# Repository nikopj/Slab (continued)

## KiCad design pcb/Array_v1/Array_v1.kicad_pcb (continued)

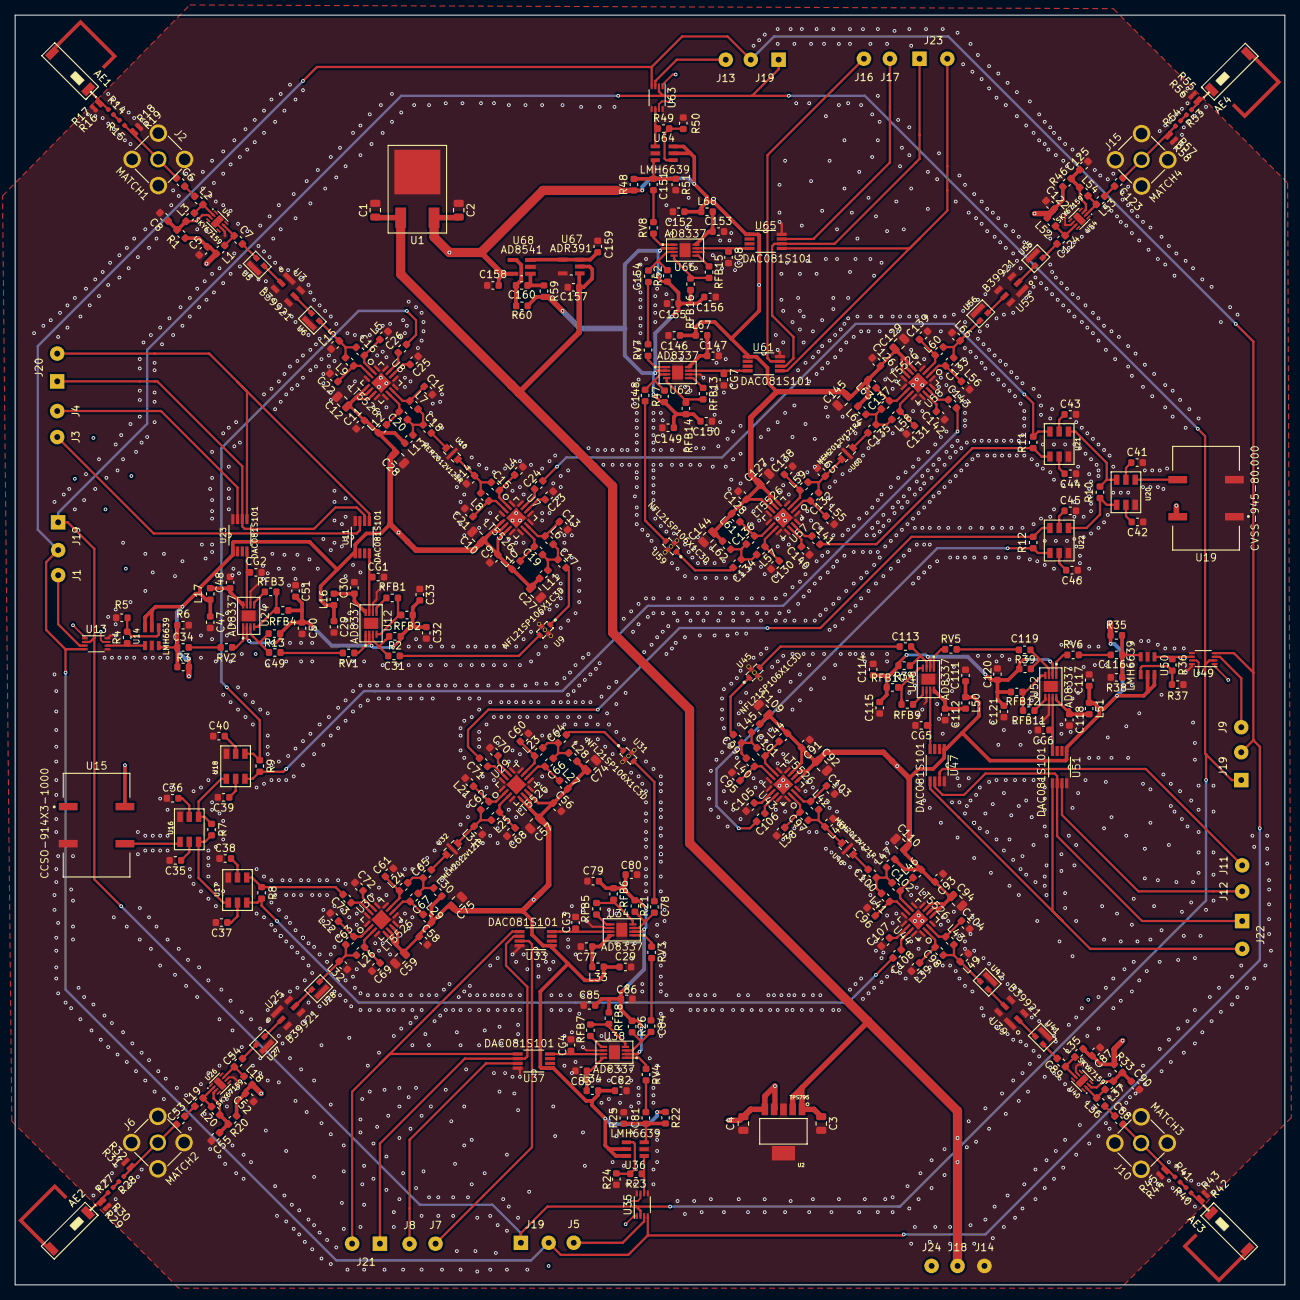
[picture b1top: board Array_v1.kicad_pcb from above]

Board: 4 copper layers, 173.9 x 173.9 mm, 419 parts (0 on the bottom side), 241 nets.

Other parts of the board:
C29#2: 10u; C_0603_1608Metric
J19#2, J19#3, J19#4: SPI_ADC; SolderWirePad_1x02_P3.81mm_Drill0.8mm

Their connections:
+5V: C29#2.1; also elsewhere on the board
GND: C29#2.2; also elsewhere on the board
SCLK_ADC: J19#2.1, J19#3.1, J19#4.1; also elsewhere on the board
~CS~_ADC: J19#2.2, J19#3.2, J19#4.2; also elsewhere on the board

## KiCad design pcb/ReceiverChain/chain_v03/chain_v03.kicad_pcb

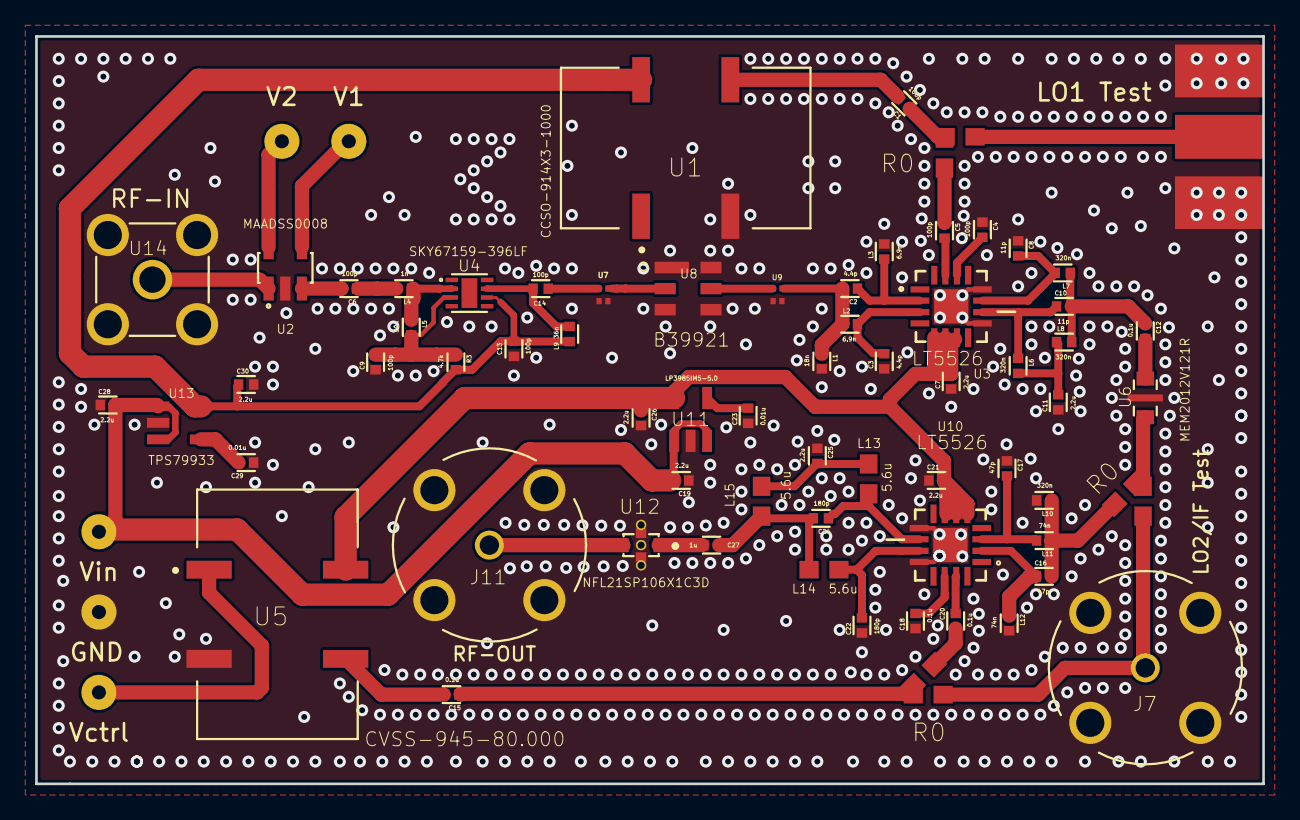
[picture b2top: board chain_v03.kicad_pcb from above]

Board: 2 copper layers, 69.8 x 42.5 mm, 74 parts (0 on the bottom side), 48 nets.

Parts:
C1, C4, C5, C6, C9, C13, C14: 100p; CAPC1005X55N
C2, C3: 4.4p; CAPC1005X55N
C7, C11, C19, C21, C25, C26, C28, C30: 2.2u; CAPC1005X55N
C8, C10: 11p; CAPC1005X55N
C12, C15, C18, C20: 0.1u; CAPC1005X55N
C16, C17: 47p; CAPC1005X55N
C22, C24: 180p; CAPC1005X55N
C23, C29: 0.01u; CAPC1005X55N
C27: 1u; CAPC1005X55N
GND: Conn_01x01_Female; SolderWirePad_1x01_Drill0.8mm
J7: LO2/IF Test; TE_5-1634503-1
J11: RF-OUT; TE_5-1634503-1
L1: 18n; CAPC1005X55N
L2, L3: 6.9n; CAPC1005X55N
L4: 1n; CAPC1005X55N
L5: 30n; CAPC1005X55N
L6, L7, L8, L10: 320n; CAPC1005X55N
L9: 36n; CAPC1005X55N
L11, L12: 74n; CAPC1005X55N
L13, L14, L15: 5.6u; 0603
LO1 Test: LO1 Test; sma-edge-16
R0, R0#2, R0#3, R1, R5, R7: 0; 0603
R3: 4.7k; CAPC1005X55N
U1: CCSO-914X3-1000; OSCSC508P1420X914X530-4N
U2: MAADSS0008; SOT95P285X145-5N
U3, U10: LT5526; QFN65P400X400X100-17N
U4: SKY67159-396LF; SON50P200X200X80-9N
U5: CVSS-945-80.000; OSCSC508P1420X914X530-4N
U6: MEM2012V121R; FIL_MEM2012V121RT001
U7, U9: PAT0510S
U8: B39921; SON120P300X300X110-6N
U11: LP3985IM5-5.0; SOT95P300X120-5N
U12: NFL21SP106X1C3D; FIL_NFM21PC105B1C3D
U13: TPS79933; SOT95P300X120-5N
U14: RF-IN; TE_5-1814832-1
V1, V2: Conn_01x01_Female; SolderWirePad_1x01_Drill0.8mm
Vctrl: Conn_01x01_Female; SolderWirePad_1x01_Drill0.8mm
Vin: Conn_01x01_Female; SolderWirePad_1x01_Drill0.8mm

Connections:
+3V3: C13.2, C30.1, L9.1, R3.2, U1.4, U4.6, U13.5
+5V: C7.2, C21.2, C26.1, U3.5, U3.6, U3.7, U5.4, U10.5, U10.6, U10.7, U11.5
GND: C3.1, C4.1, C7.1, C8.1, C9.1, C11.1, C13.1, C17.1, C18.1, C19.1, C21.1, C22.1, C23.1, C25.1, C26.2, C28.1, C29.1, C30.2, GND.1, J7.2, J7.3, J7.4, J7.5, J11.2, J11.3, J11.4, J11.5, L1.2, L3.2, L10.2, L12.2, LO1 Test.1, LO1 Test.3, LO1 Test.4, LO1 Test.5, U1.2, U2.2, U3.9, U3.12, U3.17, U5.2, U6.2, U7.3, U8.1, U8.3, U8.4, U8.6, U9.3, U10.9, U10.12, U10.17, U11.2, U12.2_1, U12.2_2, U12.S1, U12.S2, U12.S3, U13.2, U14.2, U14.3, U14.4, U14.5
LO2: C20.1, R0#2.1
unnamed: C1.1, R0.1, R1.2
unnamed: C1.2, U1.3
unnamed: C2.1, L3.1, U3.2
unnamed: C3.2, L2.2, U3.3
unnamed: C4.2, U3.14
unnamed: C5.1, R1.1
unnamed: C5.2, U3.15
unnamed: C6.1, L4.2
unnamed: C6.2, U2.3
unnamed: C8.2, L7.2, U3.11
unnamed: C9.2, L5.2, R3.1, U4.3
unnamed: C10.1, L6.1, U3.10
unnamed: C10.2, C12.1, L7.1, L8.2
unnamed: C11.2, L6.2, L8.1
unnamed: C12.2, U6.1
unnamed: C14.1, U7.1
unnamed: C14.2, L9.2, U4.7
unnamed: C15.1, R0#2.2, R7.1
unnamed: C15.2, U5.3
unnamed: C16.1, L12.1, U10.2
unnamed: C16.2, L10.1, L11.1, R0#3.2
unnamed: C17.2, L11.2, U10.3
unnamed: C18.2, U10.14
unnamed: C19.2, C28.2, U11.1, U11.3, U13.1, U13.3, Vin.1
unnamed: C20.2, U10.15
unnamed: C22.2, L14.2, U10.11
unnamed: C23.2, U11.4
unnamed: C24.1, L13.1, U10.10
unnamed: C24.2, C27.1, L14.1, L15.2
unnamed: C25.2, L13.2, L15.1
unnamed: C27.2, U12.1
unnamed: C29.2, U13.4
unnamed: U2.5, V2.1
unnamed: U2.4, V1.1
unnamed: U5.1, Vctrl.1
unnamed: J7.1, R5.2, R7.2
unnamed: J11.1, U12.3
unnamed: L4.1, L5.1, U4.2
unnamed: LO1 Test.2, R0.2
unnamed: R0#3.1, R5.1, U6.3
unnamed: U7.2, U8.2
unnamed: U8.5, U9.1
unnamed: U2.1, U14.1
RFout: C2.2, L1.1, L2.1, U9.2

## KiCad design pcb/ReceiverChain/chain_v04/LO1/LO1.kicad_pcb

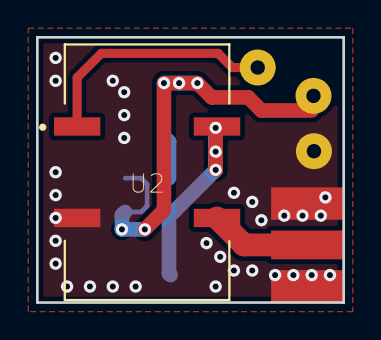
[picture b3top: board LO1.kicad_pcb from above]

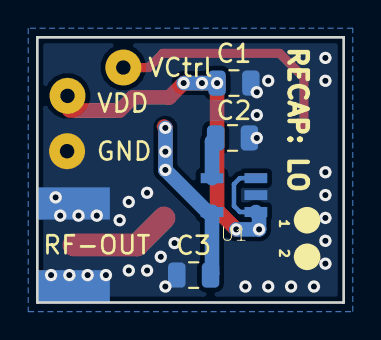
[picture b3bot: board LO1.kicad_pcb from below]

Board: 2 copper layers, 17.0 x 14.7 mm, 9 parts (4 on the bottom side), 6 nets.

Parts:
C1, C3: 2.2u; C_0805_2012Metric
C2: 0.01u; C_0805_2012Metric
GND: GND; SolderWirePad_1x01_Drill0.8mm
RF-OUT: RF-OUT; sma-edge-small
U1: VoltageReg; SOT95P300X120-5N
U2: CCSO-914X3-1000; OSCSC508P1420X914X530-4N
VCtrl: Vctrl; SolderWirePad_1x01_Drill0.8mm
VDD: VDD; SolderWirePad_1x01_Drill0.8mm

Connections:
+3V3: C3.2, U1.5, U2.4
GND: C1.2, C2.1, C3.1, GND.1, RF-OUT.2, U1.2, U2.2
unnamed: C2.2, U1.4
unnamed: U2.1, VCtrl.1
unnamed: RF-OUT.1, U2.3
VDD: C1.1, U1.1, U1.3, VDD.1

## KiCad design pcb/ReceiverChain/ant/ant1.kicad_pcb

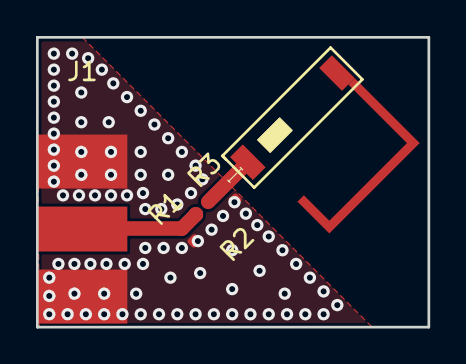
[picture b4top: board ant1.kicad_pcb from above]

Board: 2 copper layers, 21.8 x 16.1 mm, 5 parts (0 on the bottom side), 3 nets.

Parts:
AE1: Antenna_Chip; 0915AT43A0026
J1: SMA; SMA-EDGE-16
R1, R2, R3: LC; R_0402_1005Metric

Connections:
GND: J1.1, J1.2, J1.3, J1.4, R1.2, R3.2
unnamed: AE1.1, R2.1, R3.1
unnamed: J1.5, R1.1, R2.2

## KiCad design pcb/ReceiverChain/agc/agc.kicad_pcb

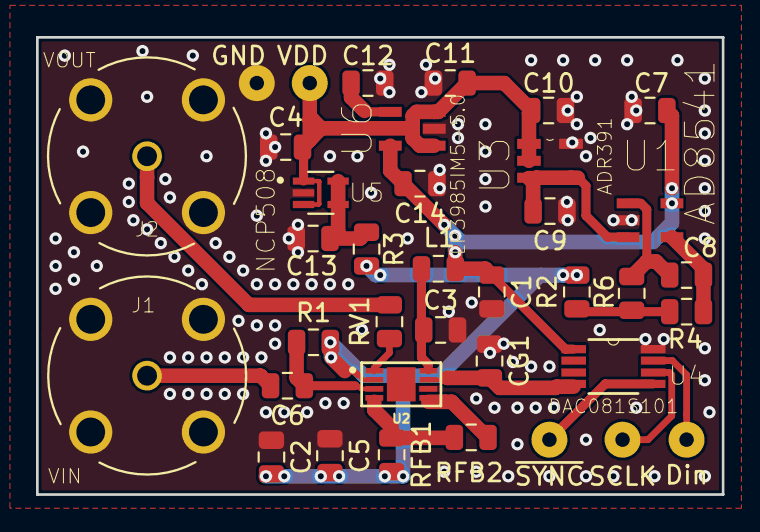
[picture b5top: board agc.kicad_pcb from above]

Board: 2 copper layers, 38.1 x 25.4 mm, 36 parts (0 on the bottom side), 20 nets.

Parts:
C1: 10u; C_0805_2012Metric
C2: 1u; C_0805_2012Metric
C3, C5, C6, C7, C9, C10, C12: 0.1u; C_0805_2012Metric
C4, C11, C13, C14: 2.2u; C_0805_2012Metric
C8: 0.22u; C_0805_2012Metric
CG1: 1nF; C_0805_2012Metric
Din: Din; SolderWirePad_1x01_Drill0.8mm
GND: GND; SolderWirePad_1x01_Drill0.8mm
J1: VIN; TE_5-1634503-1
J2: VOUT; TE_5-1634503-1
L1: 120n; C_0805_2012Metric
R1: 49.9; C_0805_2012Metric
R2, R3: 0; C_0805_2012Metric
R4: 10k; C_0805_2012Metric
R6: 100; C_0805_2012Metric
RFB1, RFB2: 100; C_0805_2012Metric
RV1: 453; C_0805_2012Metric
SCLK: SCLK; SolderWirePad_1x01_Drill0.8mm
U1: AD8541; SOT95P300X120-5N
U2: AD8337
U3: ADR391; SOT95P280X100-5N
U4: DAC081S101; SOP65P490X109-8N
U5: NCP508; SOT65P210X110-5N
U6: LP3985IM5-5.0; SOT95P300X120-5N
VDD: VDD; SolderWirePad_1x01_Drill0.8mm

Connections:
2_5: C9.2, U1.3, U3.3, U3.4
+5V: C1.1, C7.1, C14.2, L1.1, U1.5, U4.1, U6.5
GAIN: CG1.2, U2.7, U4.4
GND: C1.2, C2.1, C3.2, C4.1, C5.1, C7.2, C9.1, C10.1, C11.1, C12.1, C13.1, C14.1, CG1.1, GND.1, J1.2, J1.3, J1.4, J1.5, J2.2, J2.3, J2.4, J2.5, U1.2, U2.6, U3.5, U4.8, U5.2, U6.2
unnamed: C3.1, L1.2, U2.8
unnamed: C6.1, R1.1, U2.3
unnamed: C6.2, J1.1
unnamed: C8.1, R4.2, U1.4
unnamed: C8.2, R6.1, U1.1
unnamed: C12.2, U6.4
unnamed: C13.2, R3.1, U5.4, U5.5
unnamed: J2.1, RV1.2
unnamed: SCLK.1, U4.6
unnamed: Din.1, U4.7
unnamed: R2.1, R4.1, R6.2
unnamed: RFB1.1, RFB2.1, U2.4
unnamed: RFB2.2, U2.5
unnamed: RV1.1, U2.1
VCOM: C2.2, C5.2, R1.2, R2.2, R3.2, RFB1.2, U2.2
VDD: C4.2, C10.2, C11.2, U3.1, U3.2, U5.1, U5.3, U6.1, U6.3, VDD.1

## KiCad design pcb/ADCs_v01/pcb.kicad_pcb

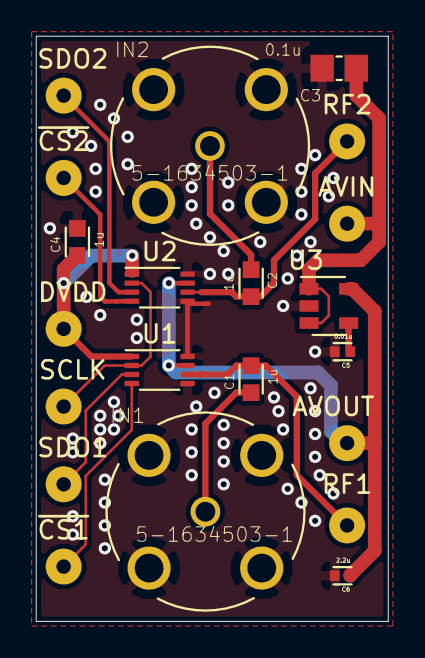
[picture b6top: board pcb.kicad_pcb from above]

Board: 2 copper layers, 19.6 x 32.5 mm, 19 parts (0 on the bottom side), 12 nets.

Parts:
AVIN: Conn_01x01_Female; SolderWirePad_1x01_Drill0.8mm
AVOUT: Conn_01x01_Female; SolderWirePad_1x01_Drill0.8mm
C1, C2, C4: 1u; CAPC1608X9N
C3: 0.1u; CAPC2012X135N
C5: 0.01u; CAPC1005X55N
C6: 2.2u; CAPC1005X55N
DVDD: Conn_01x01_Female; SolderWirePad_1x01_Drill0.8mm
IN1, IN2: 5-1634503-1; TE_5-1634503-1
RF1, RF2: Conn_01x01_Female; SolderWirePad_1x01_Drill0.8mm
SCLK: Conn_01x01_Female; SolderWirePad_1x01_Drill0.8mm
SDO1, SDO2: Conn_01x01_Female; SolderWirePad_1x01_Drill0.8mm
U1, U2: ADS7040xDCU; VSSOP-8_2.3x2mm_P0.5mm
U3: TPS79333-EP; SOT-23-5

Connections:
GND: C3.2, C4.2, C5.2, C6.2, IN1.2, IN1.3, IN1.4, IN1.5, IN2.2, IN2.3, IN2.4, IN2.5, U1.5, U1.8, U2.5, U2.8, U3.2
unnamed: C1.1, IN1.1
unnamed: C1.2, RF1.1, U1.6
unnamed: C2.1, IN2.1
unnamed: C2.2, RF2.1, U2.6
unnamed: AVIN.1, C3.1, U3.1, U3.3
unnamed: C5.1, U3.4
unnamed: SDO1.1, U1.3
unnamed: SDO2.1, U2.3
unnamed: SCLK.1, U1.2, U2.2
VAA: AVOUT.1, C6.1, U1.7, U2.7, U3.5
VDD: C4.1, DVDD.1, U1.1, U2.1

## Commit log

2018-11-03 started clean
2018-11-03 renamed misc_sims
2018-11-03 localization not working still:
2018-11-11 poster stuff
2019-02-25 slab update
2019-03-07 lets hope this works
2019-03-07 lets go
2019-03-07 bugging out
2019-03-14 stuff
2019-03-14 worm matching
2019-03-22 for karol
2019-03-23 saving
2019-03-23 almost finished assigning footprints
2019-03-23 almost done with arrayv1
2019-03-23 can't run LVS meaningfully
2019-03-24 added all gnd vias
2019-03-24 passed DRC
